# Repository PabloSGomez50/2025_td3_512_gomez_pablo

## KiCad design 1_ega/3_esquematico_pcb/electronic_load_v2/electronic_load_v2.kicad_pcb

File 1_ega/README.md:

# Proyecto Carga Electrónica Programable
Comision: 5.12 (Lunes)
Grupo: 5
Integrantes:
- Pablo Gomez

Video de funcionamiento del proyecto:
- [Link a google Drive](https://drive.google.com/file/d/1B5Tm3FmXttDTbH4h-g3oLJWiAE53vNjP/view?usp=sharing)

## Templates para informe IEEE

* [LaTeX en Overleaf](https://www.overleaf.com/latex/templates/ieee-conference-template/grfzhhncsfqn)
* [Google Docs](https://docs.google.com/document/d/1DDDHbyujVE0Jso3ITDVRpF-n_ydSYhf2IecZ8xTA-0w/preview?markAsViewed=false&tab=t.0)

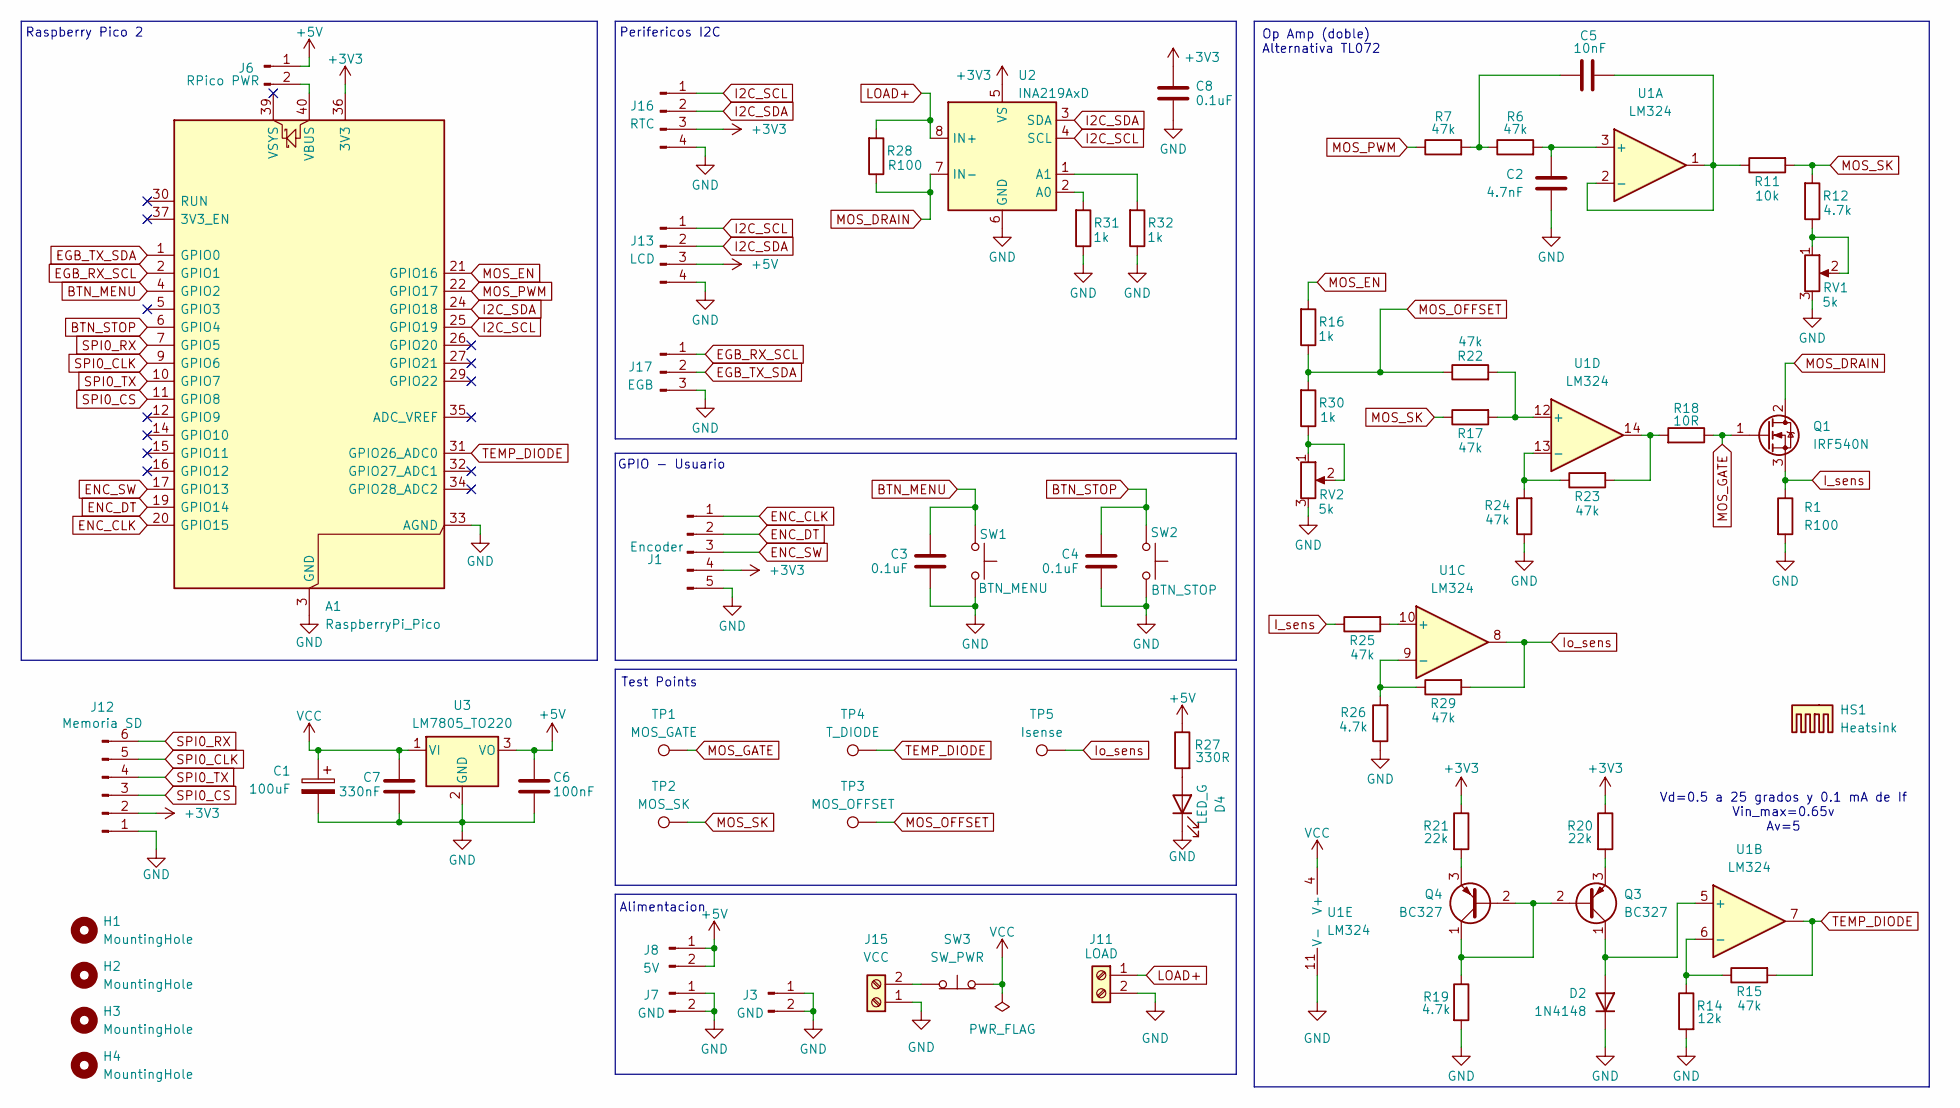
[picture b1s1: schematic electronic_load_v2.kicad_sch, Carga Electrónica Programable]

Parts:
A1: RaspberryPi_Pico; RaspberryPi_Pico_2_THT
C1: 100uF; CP_Radial_D5.0mm_P2.50mm
C2: 4.7nF; C_0805_2012Metric_Pad1.18x1.45mm_HandSolder
C3, C4, C8: 0.1uF; C_0805_2012Metric_Pad1.18x1.45mm_HandSolder
C5: 10nF; C_0805_2012Metric_Pad1.18x1.45mm_HandSolder
C6: 100nF; C_0805_2012Metric_Pad1.18x1.45mm_HandSolder
C7: 330nF; C_0805_2012Metric_Pad1.18x1.45mm_HandSolder
D2: 1N4148; D_DO-35_SOD27_P7.62mm_Horizontal
D4: LED_G; LED_D5.0mm
H1, H2, H3, H4: MountingHole; MountingHole_3.2mm_M3_DIN965
HS1: Heatsink; D-6225T
J1: Encoder; Molex_KK-254_AE-6410-05A_1x05_P2.54mm_Vertical
J3, J7: GND; PinHeader_1x02_P2.54mm_Vertical
J6: RPico PWR; PinHeader_1x02_P2.54mm_Vertical
J8: 5V; PinHeader_1x02_P2.54mm_Vertical
J11: LOAD; TerminalBlock_Phoenix_MKDS-1,5-2-5.08_1x02_P5.08mm_Horizont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
J12: Memoria SD; Molex_KK-254_AE-6410-06A_1x06_P2.54mm_Vertical
J13: LCD; Molex_KK-254_AE-6410-04A_1x04_P2.54mm_Vertical
J15: VCC; TerminalBlock_Phoenix_MKDS-1,5-2-5.08_1x02_P5.08mm_Horizont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
J16: RTC; PinHeader_1x04_P2.54mm_Vertical
J17: EGB; PinSocket_1x03_P2.54mm_Vertical
Q1: IRF540N; TO-220-3_Vertical
Q3, Q4: BC327; TO-92_Inline_Wide
R1, R28: R100; R_shunt_ina219
R6, R7, R15, R17, R22, R23, R24, R25, R29: 47k; R_1206_3216Metric_Pad1.30x1.75mm_HandSolder
R11: 10k; R_1206_3216Metric_Pad1.30x1.75mm_HandSolder
R12, R19, R26: 4.7k; R_1206_3216Metric_Pad1.30x1.75mm_HandSolder
R14: 12k; R_1206_3216Metric_Pad1.30x1.75mm_HandSolder
R16, R30, R31, R32: 1k; R_1206_3216Metric_Pad1.30x1.75mm_HandSolder
R18: 10R; R_1206_3216Metric_Pad1.30x1.75mm_HandSolder
R20, R21: 22k; R_Axial_DIN0207_L6.3mm_D2.5mm_P10.16mm_Horizontal
R27: 330R; R_0805_2012Metric_Pad1.20x1.40mm_HandSolder
RV1, RV2: 5k; Potentiometer_Bourns_3296W_Vertical
SW1: BTN_MENU; Molex_KK-254_AE-6410-02A_1x02_P2.54mm_Vertical
SW2: BTN_STOP; Molex_KK-254_AE-6410-02A_1x02_P2.54mm_Vertical
SW3: SW_PWR; Molex_KK-254_AE-6410-02A_1x02_P2.54mm_Vertical
TP1: MOS_GATE; Pin_D0.7mm_L6.5mm_W1.8mm_FlatFork
TP2: MOS_SK; Pin_D0.7mm_L6.5mm_W1.8mm_FlatFork
TP3: MOS_OFFSET; Pin_D0.7mm_L6.5mm_W1.8mm_FlatFork
TP4: T_DIODE; Pin_D0.7mm_L6.5mm_W1.8mm_FlatFork
TP5: Isense; Pin_D0.7mm_L6.5mm_W1.8mm_FlatFork
U1: LM324; DIP-14_W7.62mm_Socket
U2: INA219AxD; SOIC-8_3.9x4.9mm_P1.27mm
U3: LM7805_TO220; TO-220-3_Vertical

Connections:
+3V3: A1.36 (3V3), C8.2, J1.4, J12.2, J16.3, R20.1, R21.1, U2.5 (VS)
+5V: C6.2, J6.1, J8.1, J8.2, J13.3, R27.1, U3.3 (VO)
BTN_MENU: A1.4 (GPIO2), C3.2, SW1.2
BTN_STOP: A1.6 (GPIO4), C4.2, SW2.1
EGB_RX_SCL: A1.2 (GPIO1), J17.1
EGB_TX_SDA: A1.1 (GPIO0), J17.2
ENC_CLK: A1.20 (GPIO15), J1.1
ENC_DT: A1.19 (GPIO14), J1.2
ENC_SW: A1.17 (GPIO13), J1.3
GND: A1.3 (GND), A1.8 (GND), A1.13 (GND), A1.18 (GND), A1.23 (GND), A1.28 (GND), A1.33 (AGND), A1.38 (GND), C1.2, C2.2, C3.1, C4.1, C6.1, C7.1, C8.1, D2.1 (K), D4.1 (K), J1.5, J3.1, J3.2, J7.1, J7.2, J11.2, J12.1, J13.4, J15.1, J16.4, J17.3, R1.2, R14.2, R19.2, R24.1, R26.1, R31.1, R32.1, RV1.3, RV2.3, SW1.1, SW2.2, U1.11 (V-), U2.6 (GND), U3.2 (GND)
I2C_SCL: A1.25 (GPIO19), J13.1, J16.1, U2.4 (SCL)
I2C_SDA: A1.24 (GPIO18), J13.2, J16.2, U2.3 (SDA)
I_sens: Q1.3 (S), R1.1, R25.1
Io_sens: R29.2, TP5.1, U1.8
LOAD+: J11.1, R28.2, U2.8 (IN+)
MOS_DRAIN: Q1.2 (D), R28.1, U2.7 (IN-)
MOS_EN: A1.21 (GPIO16), R16.2
MOS_GATE: Q1.1 (G), R18.1, TP1.1
MOS_OFFSET: R16.1, R22.1, R30.2, TP3.1
MOS_PWM: A1.22 (GPIO17), R7.1
MOS_SK: R11.2, R12.2, R17.1, TP2.1
unnamed: A1.40 (VBUS), J6.2
unnamed: C5.1, R6.1, R7.2
unnamed: D2.2 (A), Q3.1 (C), U1.5 (+)
unnamed: D4.2 (A), R27.2
unnamed: J15.2, SW3.1 (A)
unnamed: Q3.2 (B), Q4.1 (C), Q4.2 (B), R19.1
unnamed: Q3.3 (E), R20.2
unnamed: Q4.3 (E), R21.2
unnamed: R12.1, RV1.1, RV1.2
unnamed: R18.2, R23.2, U1.14
unnamed: R30.1, RV2.1, RV2.2
unnamed: C2.1, R6.2, U1.3 (+)
unnamed: C5.2, R11.1, U1.1, U1.2 (-)
unnamed: R14.1, R15.1, U1.6 (-)
unnamed: R25.2, U1.10 (+)
unnamed: R26.2, R29.1, U1.9 (-)
unnamed: R17.2, R22.2, U1.12 (+)
unnamed: R23.1, R24.2, U1.13 (-)
unnamed: R31.2, U2.2 (A0)
unnamed: R32.2, U2.1 (A1)
SPI0_CLK: A1.9 (GPIO6), J12.5
SPI0_CS: A1.11 (GPIO8), J12.3
SPI0_RX: A1.7 (GPIO5), J12.6
SPI0_TX: A1.10 (GPIO7), J12.4
TEMP_DIODE: A1.31 (GPIO26_ADC0), R15.2, TP4.1, U1.7
VCC: C1.1, C7.2, SW3.2 (B), U1.4 (V+), U3.1 (VI)

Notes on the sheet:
GPIO - Usuario
Perifericos I2C
Op Amp (doble) Alternativa TL072
Alimentacion
Test Points
Raspberry Pico 2
Vd=0.5 a 25 grados y 0.1 mA de If Vin_max=0.65v Av=5

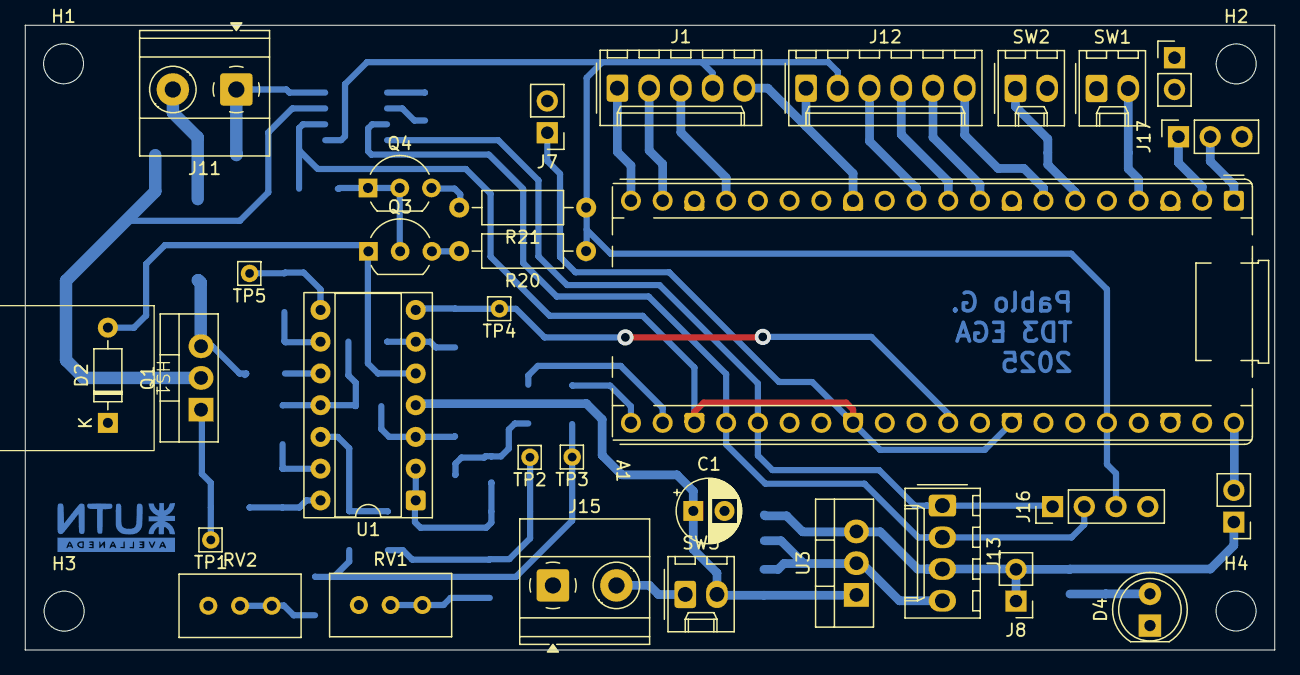
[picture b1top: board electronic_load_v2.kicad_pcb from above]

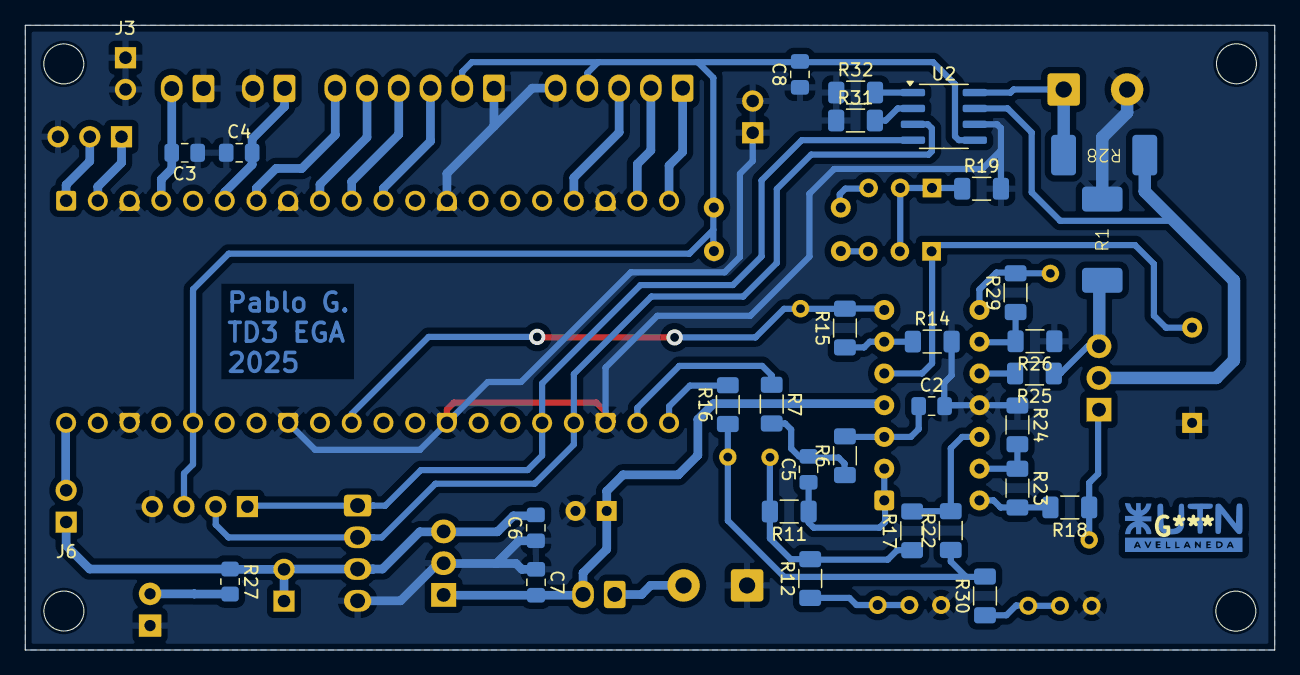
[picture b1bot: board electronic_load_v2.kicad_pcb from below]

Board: 2 copper layers, 100.0 x 50.0 mm, 67 parts (30 on the bottom side), 47 nets.

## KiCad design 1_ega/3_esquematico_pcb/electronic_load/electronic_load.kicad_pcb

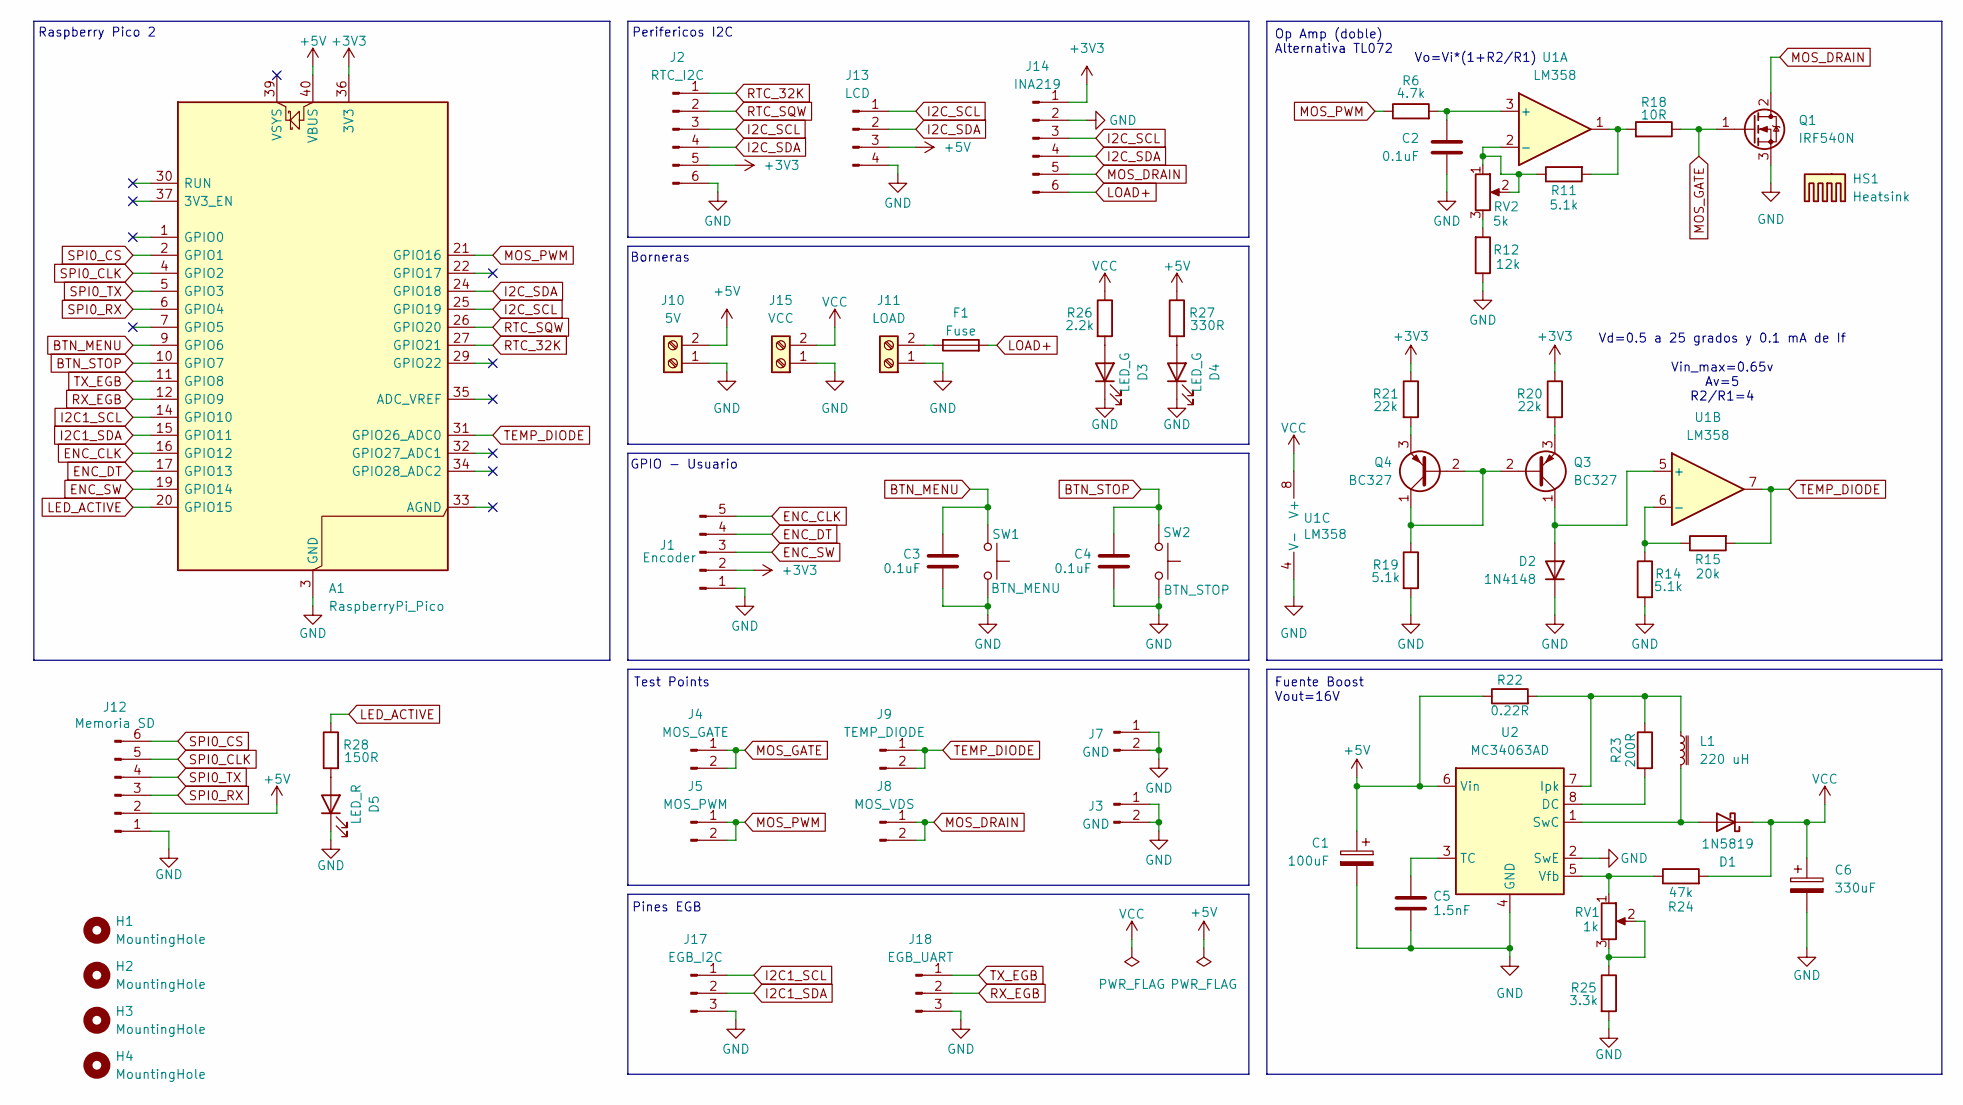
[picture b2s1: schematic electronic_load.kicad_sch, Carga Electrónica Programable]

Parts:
A1: RaspberryPi_Pico; RaspberryPi_Pico_2_THT
C1: 100uF; CP_Radial_D6.3mm_P2.50mm
C2: 0.1uF; C_Disc_D5.0mm_W2.5mm_P5.00mm
C3, C4: 0.1uF; C_Disc_D3.4mm_W2.1mm_P2.50mm
C5: 1.5nF; C_Disc_D5.0mm_W2.5mm_P5.00mm
C6: 330uF; CP_Radial_D10.0mm_P3.50mm
D1: 1N5819; D_DO-41_SOD81_P10.16mm_Horizontal
D2: 1N4148; D_DO-35_SOD27_P7.62mm_Horizontal
D3, D4: LED_G; LED_D3.0mm
D5: LED_R; LED_D3.0mm
F1: Fuse; Fuseholder_Clip-5x20mm_Eaton_1A5601-01_Inline_P20.80x6.76mm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
H1, H2, H3, H4: MountingHole; MountingHole_3.2mm_M3_DIN965
HS1: Heatsink; Heatsink_2725D
J1: Encoder; Molex_KK-254_AE-6410-05A_1x05_P2.54mm_Vertical
J2: RTC_I2C; PinSocket_1x06_P2.54mm_Vertical
J3, J7: GND; PinHeader_1x02_P2.54mm_Vertical
J4: MOS_GATE; PinHeader_1x02_P2.54mm_Vertical
J5: MOS_PWM; PinHeader_1x02_P2.54mm_Vertical
J8: MOS_VDS; PinHeader_1x02_P2.54mm_Vertical
J9: TEMP_DIODE; PinHeader_1x02_P2.54mm_Vertical
J10: 5V; TerminalBlock_Phoenix_MKDS-1,5-2-5.08_1x02_P5.08mm_Horizont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
J11: LOAD; TerminalBlock_Phoenix_MKDS-1,5-2-5.08_1x02_P5.08mm_Horizont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
J12: Memoria SD; Molex_KK-254_AE-6410-06A_1x06_P2.54mm_Vertical
J13: LCD; Molex_KK-254_AE-6410-04A_1x04_P2.54mm_Vertical
J14: INA219
J15: VCC; TerminalBlock_Phoenix_MKDS-1,5-2-5.08_1x02_P5.08mm_Horizont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
J17: EGB_I2C; PinSocket_1x03_P2.54mm_Vertical
J18: EGB_UART; PinSocket_1x03_P2.54mm_Vertical
L1: 220 uH; L_Radial_D7.5mm_P3.50mm_Fastron_07P
Q1: IRF540N; TO-220-3_Vertical
Q3, Q4: BC327; TO-92_Inline_Wide
R6: 4.7k; R_Axial_DIN0207_L6.3mm_D2.5mm_P10.16mm_Horizontal
R11, R14, R19: 5.1k; R_Axial_DIN0207_L6.3mm_D2.5mm_P10.16mm_Horizontal
R12: 12k; R_Axial_DIN0207_L6.3mm_D2.5mm_P10.16mm_Horizontal
R15: 20k; R_Axial_DIN0207_L6.3mm_D2.5mm_P10.16mm_Horizontal
R18: 10R; R_Axial_DIN0207_L6.3mm_D2.5mm_P10.16mm_Horizontal
R20, R21: 22k; R_Axial_DIN0207_L6.3mm_D2.5mm_P10.16mm_Horizontal
R22: 0.22R; R_Axial_DIN0207_L6.3mm_D2.5mm_P10.16mm_Horizontal
R23: 200R; R_Axial_DIN0207_L6.3mm_D2.5mm_P10.16mm_Horizontal
R24: 47k; R_Axial_DIN0207_L6.3mm_D2.5mm_P10.16mm_Horizontal
R25: 3.3k; R_Axial_DIN0207_L6.3mm_D2.5mm_P10.16mm_Horizontal
R26: 2.2k; R_Axial_DIN0207_L6.3mm_D2.5mm_P10.16mm_Horizontal
R27: 330R; R_Axial_DIN0207_L6.3mm_D2.5mm_P10.16mm_Horizontal
R28: 150R; R_Axial_DIN0207_L6.3mm_D2.5mm_P10.16mm_Horizontal
RV1: 1k; PinHeader_1x03_P2.54mm_Vertical
RV2: 5k; PinHeader_1x03_P2.54mm_Vertical
SW1: BTN_MENU; Molex_KK-254_AE-6410-02A_1x02_P2.54mm_Vertical
SW2: BTN_STOP; Molex_KK-254_AE-6410-02A_1x02_P2.54mm_Vertical
U1: LM358; DIP-8_W7.62mm_Socket_LongPads
U2: MC34063AD; SOIC-8_3.9x4.9mm_P1.27mm

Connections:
+3V3: A1.36 (3V3), J1.2, J2.5, J14.1, R20.1, R21.1
+5V: A1.40 (VBUS), C1.1, J10.2, J12.2, J13.3, R22.1, R27.1, U2.6 (Vin)
BTN_MENU: A1.9 (GPIO6), C3.2, SW1.2
BTN_STOP: A1.10 (GPIO7), C4.2, SW2.1
ENC_CLK: A1.16 (GPIO12), J1.5
ENC_DT: A1.17 (GPIO13), J1.4
ENC_SW: A1.19 (GPIO14), J1.3
GND: A1.3 (GND), A1.8 (GND), A1.13 (GND), A1.18 (GND), A1.23 (GND), A1.28 (GND), A1.38 (GND), C1.2, C2.2, C3.1, C4.1, C5.1, C6.2, D2.1 (K), D3.1 (K), D4.1 (K), D5.1 (K), J1.1, J2.6, J3.1, J3.2, J7.1, J7.2, J10.1, J11.1, J12.1, J13.4, J14.2, J15.1, J17.3, J18.3, Q1.3 (S), R12.1, R14.2, R19.2, R25.2, SW1.1, SW2.2, U1.4 (V-), U2.2 (SwE), U2.4 (GND)
I2C1_SCL: A1.14 (GPIO10), J17.1
I2C1_SDA: A1.15 (GPIO11), J17.2
I2C_SCL: A1.25 (GPIO19), J2.3, J13.1, J14.3
I2C_SDA: A1.24 (GPIO18), J2.4, J13.2, J14.4
LED_ACTIVE: A1.20 (GPIO15), R28.1
LOAD+: F1.2, J14.6
MOS_DRAIN: J8.1, J8.2, J14.5, Q1.2 (D)
MOS_GATE: J4.1, J4.2, Q1.1 (G), R18.1
MOS_PWM: A1.21 (GPIO16), J5.1, J5.2, R6.1
unnamed: D1.2 (A), L1.2, U2.1 (SwC)
unnamed: D2.2 (A), Q3.1 (C), U1.5 (+)
unnamed: D3.2 (A), R26.2
unnamed: D4.2 (A), R27.2
unnamed: D5.2 (A), R28.2
unnamed: F1.1, J11.2
unnamed: Q3.2 (B), Q4.1 (C), Q4.2 (B), R19.1
unnamed: Q3.3 (E), R20.2
unnamed: Q4.3 (E), R21.2
unnamed: R11.2, R18.2, U1.1
unnamed: R12.2, RV2.3
unnamed: R25.1, RV1.2, RV1.3
unnamed: C2.1, R6.2, U1.3 (+)
unnamed: R11.1, RV2.1, RV2.2, U1.2 (-)
unnamed: R14.1, R15.1, U1.6 (-)
unnamed: R23.2, U2.8 (DC)
unnamed: L1.1, R22.2, R23.1, U2.7 (Ipk)
unnamed: C5.2, U2.3 (TC)
unnamed: R24.1, RV1.1, U2.5 (Vfb)
RTC_32K: A1.27 (GPIO21), J2.1
RTC_SQW: A1.26 (GPIO20), J2.2
RX_EGB: A1.12 (GPIO9), J18.2
SPI0_CLK: A1.4 (GPIO2), J12.5
SPI0_CS: A1.2 (GPIO1), J12.6
SPI0_RX: A1.6 (GPIO4), J12.3
SPI0_TX: A1.5 (GPIO3), J12.4
TEMP_DIODE: A1.31 (GPIO26_ADC0), J9.1, J9.2, R15.2, U1.7
TX_EGB: A1.11 (GPIO8), J18.1
VCC: C6.1, D1.1 (K), J15.2, R24.2, R26.1, U1.8 (V+)

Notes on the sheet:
Vd=0.5 a 25 grados y 0.1 mA de If Vin_max=0.65v Av=5 R2/R1=4
Fuente Boost Vout=16V
GPIO - Usuario
Op Amp (doble) Alternativa TL072
Raspberry Pico 2
Test Points
Vo=Vi*(1+R2/R1)
Perifericos I2C
Borneras
Pines EGB

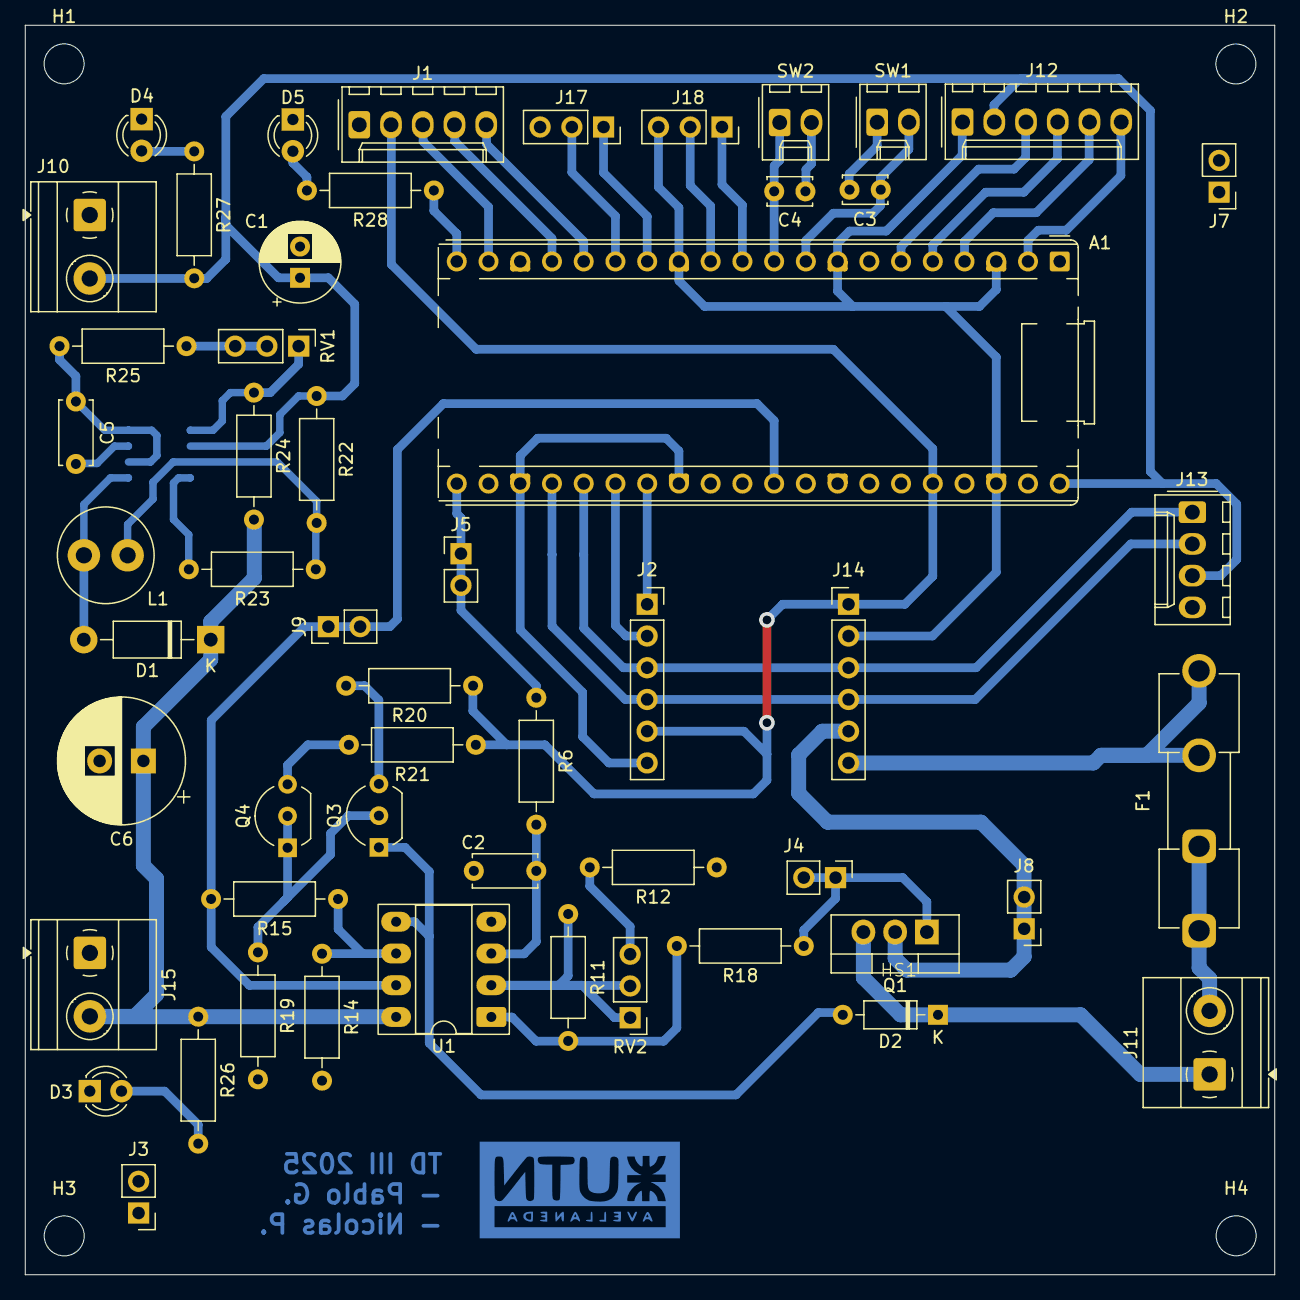
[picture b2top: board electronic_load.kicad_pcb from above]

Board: 2 copper layers, 100.0 x 100.0 mm, 60 parts (1 on the bottom side), 46 nets.

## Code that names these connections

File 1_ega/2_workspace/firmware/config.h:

#ifndef __FIRMWARE_CONFIG_H__
#define __FIRMWARE_CONFIG_H__

#include <stdio.h>
#include <string.h>
#include "hardware/i2c.h"

#include "FreeRTOS.h"
#include "task.h"
#include "queue.h"
#include "semphr.h"
#include "lcd.h"
#include "ina219.h"
#include "ds3231.h"
#include "sd_card.h"

// I2C definiciones
#define I2C_PORT i2c1
#define I2C_SDA 18
#define I2C_SCL 19
#define LCD_ADDR 0x27

#define MINIMUM_RESISTANCE 20
#define MAXIMUM_RESISTANCE 2000 // Resistencia máxima en Ohm

// Botones y Encoder
#define DEBOUNCE_TIME 50 // Tiempo de debounce en ms
#define BTN_MENU_GPIO 6
#define BTN_STOP_GPIO 7
#define BTN_SWITCH_GPIO 14
#define MAX_MENU_NUM 2

#define ENC_CHA_GPIO 12
#define ENC_CHB_GPIO 13
#define ENC_MAX_INDEX 2

// Controlador PID y protecciones
#define PWM_GAIN 1.372f
#define MAX_PWM_WRAP 12000

#define MAX_PWM_VOUT (float) (3.7f / PWM_GAIN)
#define MIN_PWM_VOUT (float) (3.02f / PWM_GAIN)

#define MAX_PWM_DUTY (uint16_t) (MAX_PWM_WRAP * MAX_PWM_VOUT / 3.3f)
#define MIN_PWM_DUTY (uint16_t) (MAX_PWM_WRAP * MIN_PWM_VOUT / 3.3f)

#define PID_STATUS_PIN 15
#define PWM_PIN 16
#define ADC_DIODE_TEMP 0 // Pin 26
#define MAX_TEMP 130.0f
#define INA219_MAX_CURRENT 0.38f
#define MAX_CURRENT 0.270f
#define MAX_VOLTAGE 12.0f

#define Kp 8.2f
#define Kd 0.032f
#define Ki 0.035f
#define MAX_INTEGRAL_VALUE 5.0f
#define MAX_DERIVATIVE_VALUE 10.0f

#define CONTROLLER_REFRESH_MS 40
#define SLEEP_INA219    30
#define SLEEP_TIME_LCD  350 // Tiempo de espera en ms para la LCD


#define USE_SERIAL_LOGGER 0
#define LOGGER_CHUNK_SIZE 100
#define LOGGER_MIN_SEND 10

typedef struct {
    uint16_t year;
    uint8_t month;
    uint8_t day;
    uint8_t hour;
    uint8_t minute;
    uint8_t second;
} rtc_data_t;

typedef enum {
    BTN_MENU,
    BTN_STOP,
    BTN_SWITCH,
    ENCODER
} btn_devices_enum;

typedef struct  {
    uint8_t gpio;
    SemaphoreHandle_t *sem_bin;
    btn_devices_enum device;
} btn_data_t;

typedef struct encoder_t {
    bool cha;
    bool chb;
} encoder_t;

typedef enum {
    MENU_MAIN = 255,
    MENU_SET_RESISTANCE = 0,
    MENU_PID = 1,
    MENU_TEST = 2,
    MENU_TIME = 3,
    MENU_SD = 4,
    // MENU_REG_FUENTE = 5,
    MENU_PROTECCION = 6
} menu_t;

typedef enum  {
    I2C_INA219,
    I2C_LCD,
    I2C_RTC
} i2c_devices_enum;

typedef struct {
    i2c_devices_enum device;
    QueueHandle_t queue;
    void (*callback)(void * param);
    void * param;
} i2c_guard_t;

typedef struct {
    btn_devices_enum device;
    bool increment;
} input_data_t;

typedef struct {
    menu_t menu;
    uint8_t index;
    bool fixed_index;
    bool sd_mounted;

    bool pid_enabled;
    uint16_t pid_time_ms;
    uint16_t pwm_value;
    
    uint16_t resistance_target;
    int16_t resistance_adj;
} system_config_t;

typedef struct {
    float kp;
    float ki;
    float kd;
    uint16_t r_target;
    uint16_t pid_time;
} pid_config_t;

typedef struct {
    float voltage_v;
    float current_ma;
    uint16_t pwm_value;
    float error;
    float integral;
    float derivative;
    uint16_t r_target;
    float temperature;
} datalogger_t;

typedef struct {
    uint16_t pid_time_ms;
    uint16_t r_target;
    uint8_t r_step_idx;
} config_t;

typedef enum {
    CONFIG_FILE,
    LOG_FILE
} sd_input_t;

typedef struct {
    sd_input_t type;
    void *data;
    uint8_t chunk_index;
} sd_event_t;

const char file_header[] = "Voltage;Current;PWM Value;Error;Integral;Derivative;R_Target;Temperature\n";
const uint8_t r_steps[] = {1, 10, 50, 100, 250};

void btn_irq_handler(uint gpio, uint32_t events);
void task_encoder(void *pvParameters);
void task_btn_pull_up(void *pvParameters);
void task_pid_controller(void *pvParameters);
void task_i2c_guard(void *pvParameters);
void task_ina219(void *pvParameters);
void task_lcd_display(void *pvParameters);
void task_read_temp(void *pvParameters);
void task_rtc(void *pvParameters);

void setup_pwm(uint8_t gpio);
void set_lcd_text(void *text);
void limit_float(float *value, float max);
void wrap_index(uint8_t *index, uint8_t max_index, bool increment);

#endif // __FIRMWARE_CONFIG_H__

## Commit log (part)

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2025-05-26 Primer consigna de TP2
2025-05-26 Segunda consigna de TP2
2025-06-02 init tp3
2025-06-03 Primera consigna TP3
2025-06-03 Segunda consigna TP3
2025-06-03 Add datasheet info of on-chip temperature sensor
2025-06-12 Primer consigna de TP4
2025-06-26 Segunda consigna de TP4
2025-06-28 add: first changes in pcb
2025-06-28 add: hoja de calculos y prueba de filtro pasa bajos en Tina
2025-06-28 chore: add datasheets in readme
2025-06-28 chore: add firmware folder
2025-06-30 feat: primera version del esquematico con valores calculados
2025-06-30 feat: replicate tp4 version for ega
2025-06-30 chore: add new references
2025-07-01 add: diagrama de conexiones y modificar firmware
2025-07-02 fix: button task and initial task_read_adc
2025-07-02 mod: change TL084 for LM324
2025-07-05 pruebas esquematico
2025-07-07 chore: mover diagrama a 1_informes
2025-07-10 rev: modify the values and validate current source for 1N4148
2025-07-10 add: encoder debounce working
2025-07-12 feat: add ina219 library
2025-07-15 test version of i2c_guard
2025-07-16 feat: task_i2c_guard v1 working. Changes in ina219 codebase
2025-07-16 feat: schematic and pcb full v1
2025-07-16 chore: migrate from mathcad to jupyter notebook
2025-07-16 chore: add guia_de_codigo
2025-07-16 chore: move guia_de_codigo
2025-07-16 feat: add sd card module pins and leds
2025-07-18 feat: pcb v2
2025-07-18 feat: fix and test ina219 library
2025-07-19 pcb small changes
2025-07-28 chore: add mounting hole to pcb
2025-07-28 minor changes to firmware
2025-07-28 chore: add pdfs
2025-07-28 add task to handle inputs
2025-08-01 minor changes to pcb MOSFET position
2025-08-05 add rtc and pcb changes
2025-08-05 feat: add sd_card
2025-08-05 chore: add example for sd_card
2025-08-09 add rtc and sd
2025-08-09 Update last version of pcb
2025-08-09 chore: add values of vgs
2025-08-11 chore: improve pid task
2025-08-11 fix error in ina219. chore: modify rtc and lcd for init via guard
2025-08-11 chore: update menu for scrolling
2025-08-12 update pcb to last version
2025-08-12 chore: update guia_de_codigo y diagrama en bloques
2025-08-12 feat: sd funcionando en datalogger y arreglo en libreria ina219
2025-08-12 add stl
2025-08-13 fix scale of ina219 current. First working pid
2025-08-13 feat: average of 4 samples before read ina219
2025-08-13 Add grapth.ipynb
2025-08-14 feat: add range of resistance for kp values
2025-08-14 feat: RTC and SD menus working
2025-08-15 chore improve graph
2025-08-15 stage code
2025-08-16 progress: logger working only in pid stable
2025-08-17 chore: ajust for all range
2025-08-17 chore: add slope input
2025-08-18 add temperature info in PID menu
2025-08-18 Final changes to code
2025-08-18 test at diferent resistance ranges
2025-08-18 chore: update PCB pdf to final version
2025-08-18 chore: cargar informe final
2025-08-19 chore: rename info in 1_informes. Add Datasheets
2025-08-21 chore: ordenar 4_anexos
2025-08-24 test filters
2025-08-25 chore: calculos de combinacion de filtros y sensiblidad de pwm
2025-08-25 feat: esquematico nuevo y footprint D-6225T
2025-08-25 chore: pwm_offset con gpio
2025-08-26 perf: resistencias a huellas smd y preliminar de segunda version de pcb
2025-08-27 chore: pcb v1 10x5 con R y C smd. INA modulo
2025-08-27 chore: minimal revision
2025-08-27 chore: ajustar valores de resistencias
2025-08-29 perf: ajustes en pistas y clearance para cnc
2025-08-29 fix: footprint de R shunt. chore: separar los componentes en la zona del operacional
2025-09-03 chore: add to-do in readme
2025-09-15 fix: add text and logo
2025-09-23 add: change Rsense to ina smd size
2025-09-29 Primer consigna de TP5
2025-09-30 Segunda consigna de TP5
2025-10-06 chore: add name and logo
2025-10-08 gerbers v2
2025-10-13 chore: add name and UTN Logo
2025-10-30 chore: load files in egb init
2025-11-02 chore: fix makefile to lead devtree
2025-11-03 chore: change task_pid_controller to eliminate and recreate
2025-11-03 chore: enable protection and simplify pid_controller
2025-11-04 test: uart in char device working
2025-11-06 chore: reassign pinout and manage test pwm
2025-11-07 chore: add basic task_uart
2025-11-08 chore: add btn stop relations
2025-11-10 chore: change pins and test pwm
2025-11-11 feat: uart works with cli app
2025-11-12 chore: manejo de mensajes de uart con egb
2025-11-13 feat: single char device with queue
2025-11-13 chore: add char dev data and command
2025-11-13 chore: only send full messages
2025-11-15 feat: presentacion congreso
2025-11-17 feat: entrega informe
2025-11-26 feat: add app and cuestionario
2025-12-10 chore: add video link
